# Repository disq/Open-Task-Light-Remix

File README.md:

# Open Task Light Remix

## ⚠️ NOT FINISHED YET

This is a work in progress: parts are still being printed, tested and changed.

A remix of [Open Task Light](https://github.com/stevenbennett/Open-Task-Light) by Steven Bennett: a new control board for the head running ESPHome, a USB-C PD board in the freestanding base with the printed parts to hold it, and fixes for printed parts that don't fit. The rest of the lamp is built as upstream.

| Folder | What's in it |
|---|---|
| [`electronics/`](electronics/) | KiCad 10 projects, Gerbers, BOMs and JLC placement files for two boards: the head's control board, reworked around a Seeed XIAO ESP32-C6, and a USB-PD board that powers the lamp at 20 V from a USB-C charger. |
| [`esphome/`](esphome/) | ESPHome firmware for the control board, for Home Assistant. |
| [`mechanical/`](mechanical/) | Printed parts: the freestanding base reworked for the PD board, wider button sockets for the electronics housing, and a lead counterweight lid that goes in. |

Each folder has its own README with the details.

## Licence

MIT, like upstream. See [LICENSE](LICENSE).

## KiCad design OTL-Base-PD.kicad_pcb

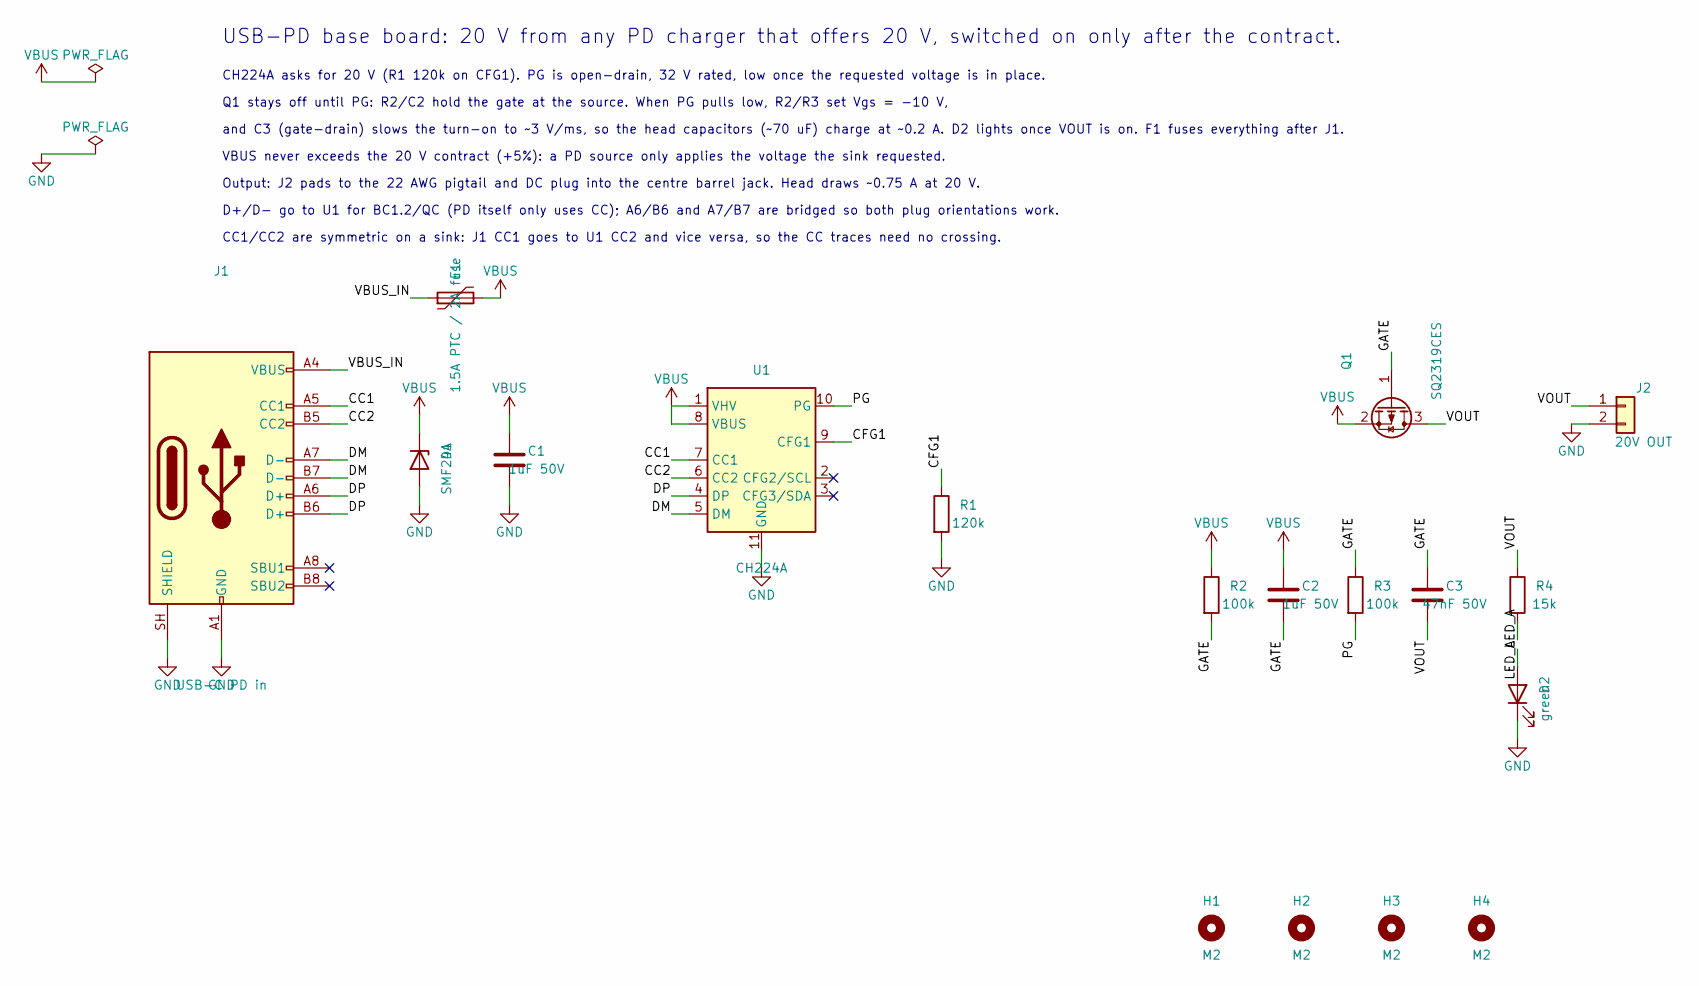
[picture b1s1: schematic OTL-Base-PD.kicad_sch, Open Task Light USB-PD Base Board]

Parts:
C1, C2: 1uF 50V; C_0805_2012Metric; MPN CL21B105KBFNNNE; LCSC Part C28323
C3: 47nF 50V; C_0603_1608Metric; MPN CL10B473KB8NNNC; LCSC Part C1622
D1: SMF24A; SOD-123F_L2.8-W1.8-LS3.7-RD; MPN SMF24A; LCSC Part C169430
D2: green; LED_0603_1608Metric; MPN XL-1608UGC-04; LCSC Part C965804
F1: 1.5A PTC / 2A fuse; Fuse_1812_1206_Dual; MPN SMD1812P150TF/33 (or Littelfuse 0466002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; LCSC Part C46970909
H1, H2, H3, H4: M2; MountingHole_2.2mm_M2
J1: USB-C PD in; USB_C_Receptacle_HRO_TYPE-C-31-M-12; MPN TYPE-C-31-M-12; LCSC Part C165948
J2: 20V OUT; SolderWire-0.5sqmm_1x02_P4.6mm_D0.9mm_OD2.1mm
Q1: SQ2319CES; SOT-23; MPN SQ2319CES-T1_GE3 (or AO3407A); LCSC Part C30884362
R1: 120k; R_0603_1608Metric; MPN 0603WAF1203T5E; LCSC Part C25808
R2, R3: 100k; R_0603_1608Metric; MPN 0603WAF1003T5E; LCSC Part C25803
R4: 15k; R_0603_1608Metric; MPN 0603WAF1502T5E; LCSC Part C22809
U1: CH224A; SSOP-10-1EP_3.9x4.9mm_P1mm_EP2.1x3.3mm_ThermalVias; MPN CH224A; LCSC Part C42459160

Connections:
/CC1: J1.A5 (CC1), U1.7 (CC1)
/CC2: J1.B5 (CC2), U1.6 (CC2)
/CFG1: R1.1, U1.9 (CFG1)
/DM: J1.A7 (D-), J1.B7 (D-), U1.5 (DM)
/DP: J1.A6 (D+), J1.B6 (D+), U1.4 (DP)
/GATE: C2.2, C3.1, Q1.1 (G), R2.2, R3.1
/LED_A: D2.2 (A), R4.2
/PG: R3.2, U1.10 (PG)
/VBUS_IN: F1.1, J1.A4 (VBUS), J1.A9 (VBUS), J1.B4 (VBUS), J1.B9 (VBUS)
/VOUT: C3.2, J2.1, Q1.3 (D), R4.1
GND: C1.2, D1.2 (A), D2.1 (K), J1.A1 (GND), J1.A12 (GND), J1.B1 (GND), J1.B12 (GND), J1.SH (SHIELD), J2.2, R1.2, U1.11 (GND)
VBUS: C1.1, C2.1, D1.1 (K), F1.2, Q1.2 (S), R2.1, U1.1 (VHV), U1.8 (VBUS)

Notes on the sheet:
CC1/CC2 are symmetric on a sink: J1 CC1 goes to U1 CC2 and vice versa, so the CC traces need no crossing.
VBUS never exceeds the 20 V contract (+5%): a PD source only applies the voltage the sink requested.
and C3 (gate-drain) slows the turn-on to ~3 V/ms, so the head capacitors (~70 uF) charge at ~0.2 A. D2 lights once VOUT is on. F1 fuses everything after J1.
D+/D- go to U1 for BC1.2/QC (PD itself only uses CC); A6/B6 and A7/B7 are bridged so both plug orientations work.
CH224A asks for 20 V (R1 120k on CFG1). PG is open-drain, 32 V rated, low once the requested voltage is in place.
USB-PD base board: 20 V from any PD charger that offers 20 V, switched on only after the contract.
Output: J2 pads to the 22 AWG pigtail and DC plug into the centre barrel jack. Head draws ~0.75 A at 20 V.
Q1 stays off until PG: R2/C2 hold the gate at the source. When PG pulls low, R2/R3 set Vgs = -10 V,

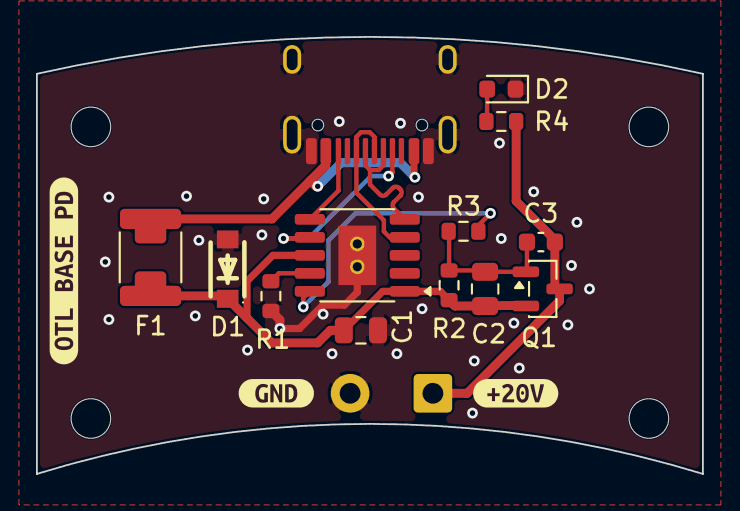
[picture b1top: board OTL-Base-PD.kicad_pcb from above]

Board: 2 copper layers, 37.0 x 24.3 mm, 21 parts (0 on the bottom side), 12 nets.

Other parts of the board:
kibuzzard-6ACABDDA: G***; kibuzzard-6ACABDDA
kibuzzard-6ACABDE6: G***; kibuzzard-6ACABDE6
kibuzzard-6ACABDF7: G***; kibuzzard-6ACABDF7

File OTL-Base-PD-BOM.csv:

"Comment","Designator","Footprint","LCSC Part #","MPN","Qty"
"1uF 50V","C1,C2","Capacitor_SMD:C_0805_2012Metric","C28323","CL21B105KBFNNNE","2"
"47nF 50V","C3","Capacitor_SMD:C_0603_1608Metric","C1622","CL10B473KB8NNNC","1"
"SMF24A","D1","EasyEDA:SOD-123F_L2.8-W1.8-LS3.7-RD","C169430","SMF24A","1"
"green","D2","LED_SMD:LED_0603_1608Metric","C965804","XL-1608UGC-04","1"
"1.5A PTC / 2A fuse","F1","OTL:Fuse_1812_1206_Dual","C46970909","SMD1812P150TF/33 (or Littelfuse 0466002.NRHF 1206 2A fuse)","1"
"USB-C PD in","J1","Connector_USB:USB_C_Receptacle_HRO_TYPE-C-31-M-12","C165948","TYPE-C-31-M-12","1"
"SQ2319CES","Q1","Package_TO_SOT_SMD:SOT-23","C30884362","SQ2319CES-T1_GE3 (or AO3407A)","1"
"120k","R1","Resistor_SMD:R_0603_1608Metric","C25808","0603WAF1203T5E","1"
"100k","R2,R3","Resistor_SMD:R_0603_1608Metric","C25803","0603WAF1003T5E","2"
"15k","R4","Resistor_SMD:R_0603_1608Metric","C22809","0603WAF1502T5E","1"
"CH224A","U1","Package_SO:SSOP-10-1EP_3.9x4.9mm_P1mm_EP2.1x3.3mm_ThermalVias","C42459160","CH224A","1"

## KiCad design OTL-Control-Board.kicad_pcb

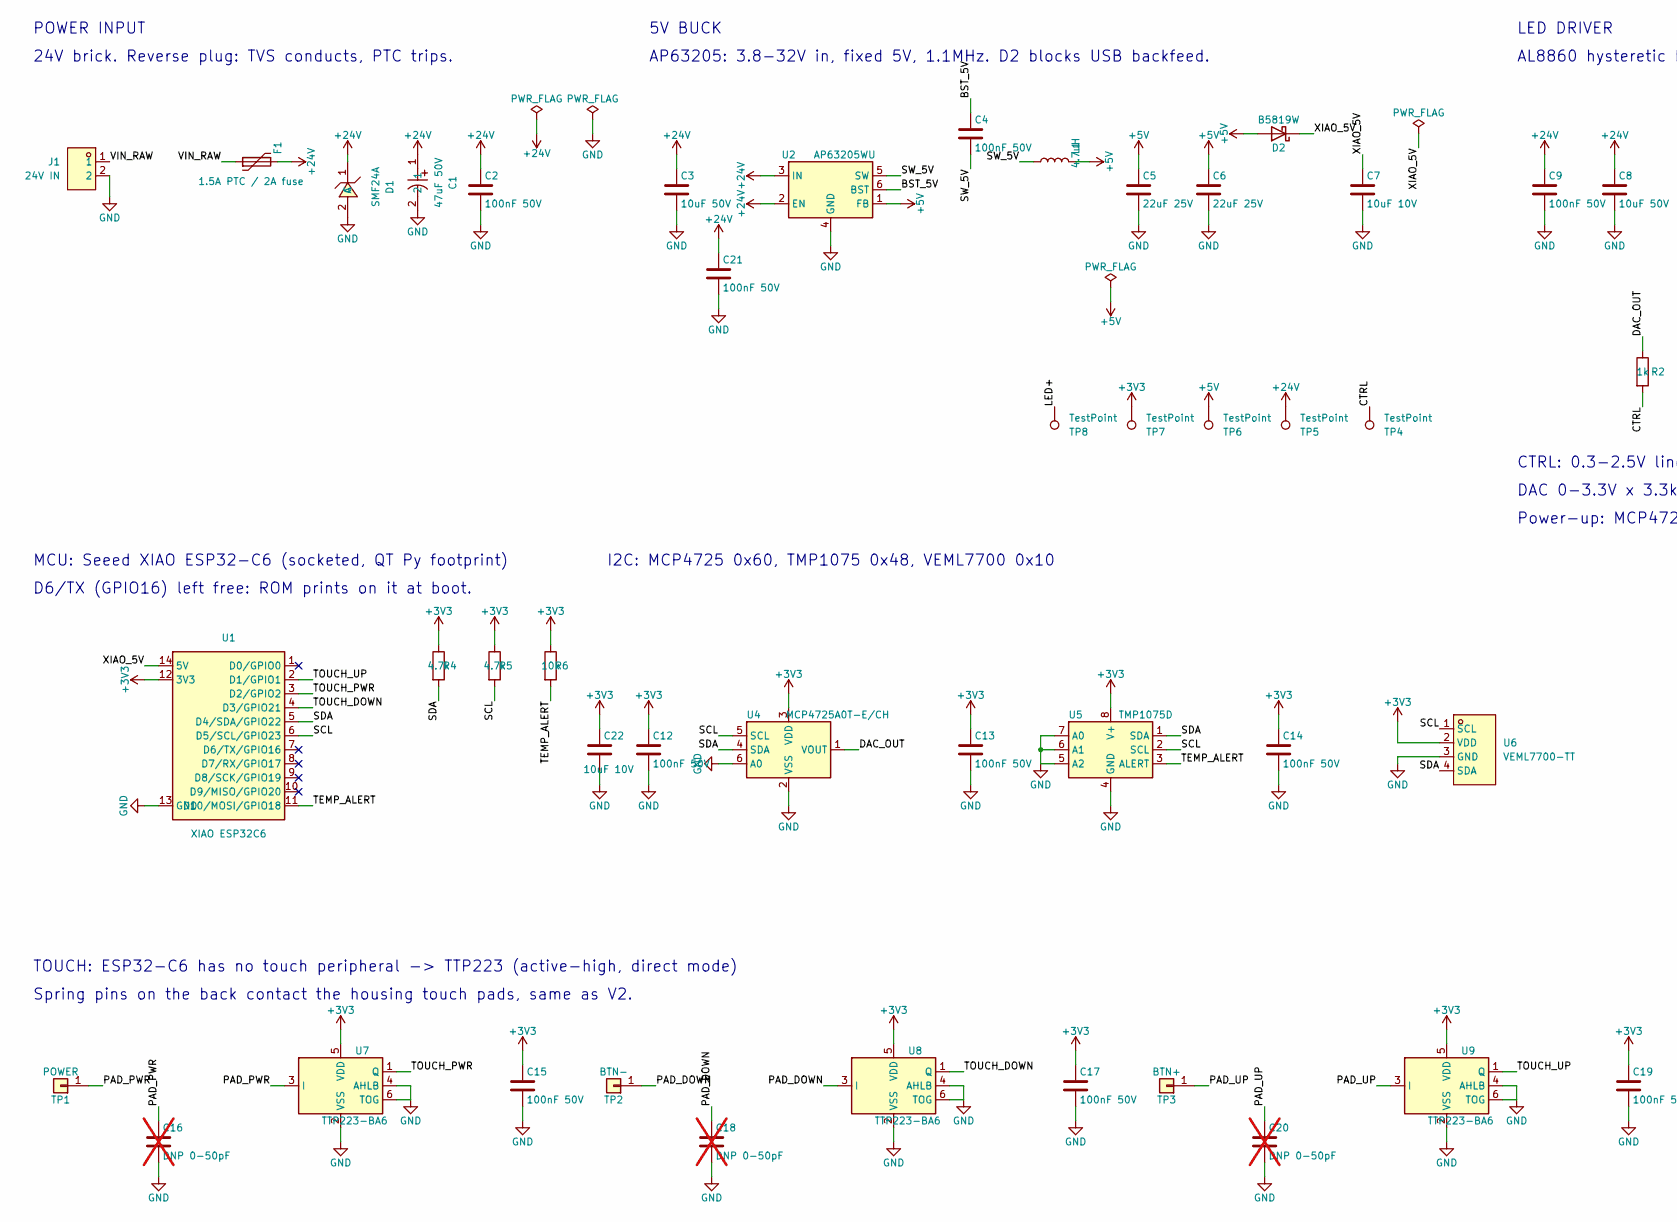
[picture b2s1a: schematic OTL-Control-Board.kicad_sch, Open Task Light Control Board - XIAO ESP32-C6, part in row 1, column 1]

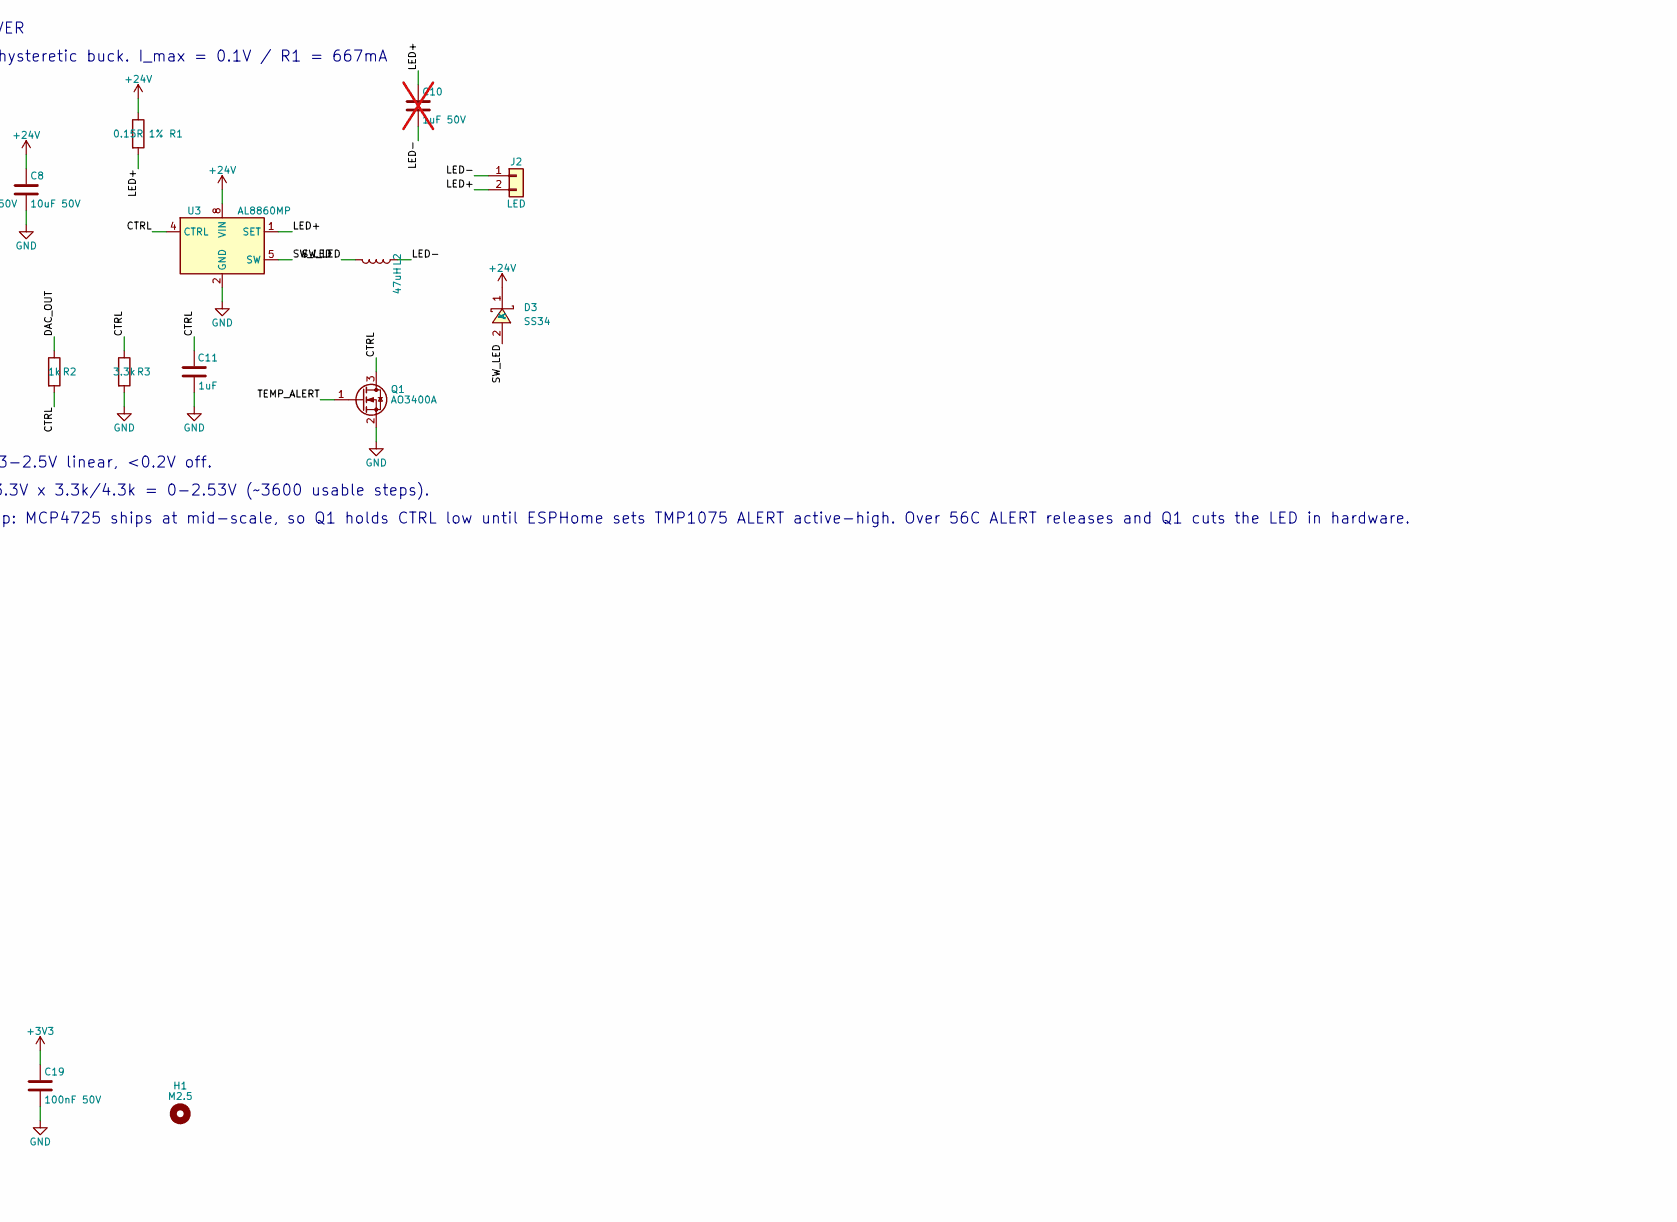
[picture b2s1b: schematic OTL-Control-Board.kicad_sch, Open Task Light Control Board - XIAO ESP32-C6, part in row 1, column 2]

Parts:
C1: 47uF 50V; CAP-SMD_BD6.3-L6.6-W6.6-FD-A; MPN VZT470M1HTR-0606; LCSC Part C688950
C2, C4, C9, C12, C13, C14, C15, C17, C19: 100nF 50V; C_0603_1608Metric; MPN CC0603KRX7R9BB104; LCSC Part C14663
C3, C8: 10uF 50V; C_1206_3216Metric; MPN 1206 X5R/X7R 10uF 50V; LCSC Part C13585
C5, C6: 22uF 25V; C_1206_3216Metric; MPN 1206 X5R 22uF 25V (CL31A226KAHNNNE); LCSC Part C12891
C7, C22: 10uF 10V; C_0805_2012Metric; MPN 0805 X5R 10uF 10V; LCSC Part C15850
C10: 1uF 50V; C_1206_3216Metric; MPN 1206 X7R 1uF 50V (optional ripple cap); LCSC Part C1848; not fitted
C11: 1uF; C_0603_1608Metric; MPN 0603 X5R 1uF; LCSC Part C15849
C16, C18, C20: DNP 0-50pF; C_0603_1608Metric; MPN sensitivity trim, C0G; not fitted
C21: 100nF 50V; C_0805_2012Metric; MPN 0805 X7R 100nF 50V (CC0805KRX7R9BB104); LCSC Part C49678
D1: SMF24A; SOD-123F_L2.8-W1.8-LS3.7-RD; MPN SMF24A; LCSC Part C169430
D2: B5819W; D_SOD-123; MPN B5819W; LCSC Part C8598
D3: SS34; SMA_L4.3-W2.6-LS5.2-RD; MPN SS34; LCSC Part C8678
F1: 1.5A PTC / 2A fuse; Fuse_1812_1206_Dual; MPN SMD1812P150TF/33 (1812 PTC, JLC reflow)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; LCSC Part C46970909
H1: M2.5; MountingHole_2.5mm_Plated
J1: 24V IN; CONN-TH_2P-P1.25-220098-0271; MPN 2200980271; LCSC Part C19803189
J2: LED; Molex_MicroLock_2200970271_V; MPN Molex 2200970271; LCSC Part C19803164
L1: 4.7uH; L_Changjiang_FNR4030S; MPN FNR4030S4R7MT (4x4, Isat>=1.5A); LCSC Part C167874
L2: 47uH; L_SRN1060_FNR8040_Dual; MPN FNR8040S470MT (8x8) or SRN1060-470M (10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; LCSC Part C168137
Q1: AO3400A; SOT-23; MPN AO3400A; LCSC Part C20917
R1: 0.15R 1%; R_1206_3216Metric; MPN 1206 0.15R 1% 0.25W; LCSC Part C5127776
R2: 1k; R_0603_1608Metric; MPN 0603 1k 1%; LCSC Part C21190
R3: 3.3k; R_0603_1608Metric; MPN 0603 3.3k 1%; LCSC Part C22978
R4, R5: 4.7k; R_0603_1608Metric; MPN 0603 4.7k; LCSC Part C23162
R6: 10k; R_0603_1608Metric; MPN 0603 10k; LCSC Part C25804
TP1: POWER; MillMax_807_SpringPin; MPN Mill-Max 807-22-001-10-001101
TP2: BTN-; MillMax_807_SpringPin; MPN Mill-Max 807-22-001-10-001101
TP3: BTN+; MillMax_807_SpringPin; MPN Mill-Max 807-22-001-10-001101
TP4, TP5, TP6, TP7, TP8: TestPoint; TestPoint_Pad_1.5x1.5mm
U1: XIAO ESP32C6; XIAO_Socket_2x7; MPN Seeed XIAO ESP32-C6 + 2x Samtec CES-107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
U2: AP63205WU; TSOT-23-6; MPN AP63205WU-7; LCSC Part C2071056
U3: AL8860MP; MSOP-8-1EP_3x3mm_P0.65mm_EP1.5x1.8mm; MPN AL8860MP-13; LCSC Part C500782
U4: MCP4725A0T-E/CH; SOT-23-6; MPN MCP4725A0T-E/CH; LCSC Part C144198
U5: TMP1075D; SOIC-8_3.9x4.9mm_P1.27mm; MPN TMP1075DR; LCSC Part C2878381
U6: VEML7700-TT; SENSOR-SMD_EML7700-TT; MPN VEML7700-TT; LCSC Part C1850416
U7, U8, U9: TTP223-BA6; SOT-23-6; MPN TTP223-BA6 or TTP223-BA6-TD; LCSC Part C42422127

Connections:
+3V3: C12.1, C13.1, C14.1, C15.1, C17.1, C19.1, C22.1, R4.1, R5.1, R6.1, TP7.1 (1_1), U1.12 (3V3), U4.3 (VDD), U5.8 (V+), U6.2 (VDD), U7.5 (VDD), U8.5 (VDD), U9.5 (VDD)
+5V: C5.1, C6.1, D2.2 (A), L1.2, TP6.1 (1_1), U2.1 (FB)
+24V: C1.1, C2.1, C3.1, C8.1, C9.1, C21.1, D1.1 (C), D3.1 (K), F1.2, R1.1, TP5.1 (1_1), U2.2 (EN), U2.3 (IN), U3.8 (VIN)
/BST_5V: C4.1, U2.6 (BST)
/CTRL: C11.1, Q1.3 (D), R2.2, R3.1, TP4.1 (1_1), U3.4 (CTRL)
/DAC_OUT: R2.1, U4.1 (VOUT)
/LED+: C10.1, J2.2, R1.2, TP8.1 (1_1), U3.1 (SET)
/LED-: C10.2, J2.1, L2.1
/PAD_DOWN: C18.1, TP2.1 (Pin_1_1), U8.3 (I)
/PAD_PWR: C16.1, TP1.1 (Pin_1_1), U7.3 (I)
/PAD_UP: C20.1, TP3.1 (Pin_1_1), U9.3 (I)
/SCL: R5.2, U1.6 (D5/SCL/GPIO23), U4.5 (SCL), U5.2 (SCL), U6.1 (SCL)
/SDA: R4.2, U1.5 (D4/SDA/GPIO22), U4.4 (SDA), U5.1 (SDA), U6.4 (SDA)
/SW_5V: C4.2, L1.1, U2.5 (SW)
/SW_LED: D3.2 (A), L2.2, U3.5 (SW), U3.6 (SW)
/TEMP_ALERT: Q1.1 (G), R6.2, U1.11 (D10/MOSI/GPIO18), U5.3 (ALERT)
/TOUCH_DOWN: U1.4 (D3/GPIO21), U8.1 (Q)
/TOUCH_PWR: U1.3 (D2/GPIO2), U7.1 (Q)
/TOUCH_UP: U1.2 (D1/GPIO1), U9.1 (Q)
/VIN_RAW: F1.1, J1.1
/XIAO_5V: C7.1, D2.1 (K), U1.14 (5V)
GND: C1.2, C2.2, C3.2, C5.2, C6.2, C7.2, C8.2, C9.2, C11.2, C12.2, C13.2, C14.2, C15.2, C16.2, C17.2, C18.2, C19.2, C20.2, C21.2, C22.2, D1.2 (A), J1.2, Q1.2 (S), R3.2, U1.13 (GND), U2.4 (GND), U3.2 (GND), U3.3 (GND), U3.9 (GND), U4.2 (VSS), U4.6 (A0), U5.4 (GND), U5.5 (A2), U5.6 (A1), U5.7 (A0), U6.3 (GND), U7.2 (VSS), U7.4 (AHLB), U7.6 (TOG), U8.2 (VSS), U8.4 (AHLB), U8.6 (TOG), U9.2 (VSS), U9.4 (AHLB), U9.6 (TOG)

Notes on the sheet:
AP63205: 3.8-32V in, fixed 5V, 1.1MHz. D2 blocks USB backfeed.
D6/TX (GPIO16) left free: ROM prints on it at boot.
DAC 0-3.3V x 3.3k/4.3k = 0-2.53V (~3600 usable steps).
AL8860 hysteretic buck. I_max = 0.1V / R1 = 667mA
24V brick. Reverse plug: TVS conducts, PTC trips.
TOUCH: ESP32-C6 has no touch peripheral -> TTP223 (active-high, direct mode)
Power-up: MCP4725 ships at mid-scale, so Q1 holds CTRL low until ESPHome sets TMP1075 ALERT active-high. Over 56C ALERT releases and Q1 cuts the LED in hardware.
I2C: MCP4725 0x60, TMP1075 0x48, VEML7700 0x10
MCU: Seeed XIAO ESP32-C6 (socketed, QT Py footprint)
LED DRIVER
5V BUCK
Spring pins on the back contact the housing touch pads, same as V2.
POWER INPUT
CTRL: 0.3-2.5V linear, <0.2V off.

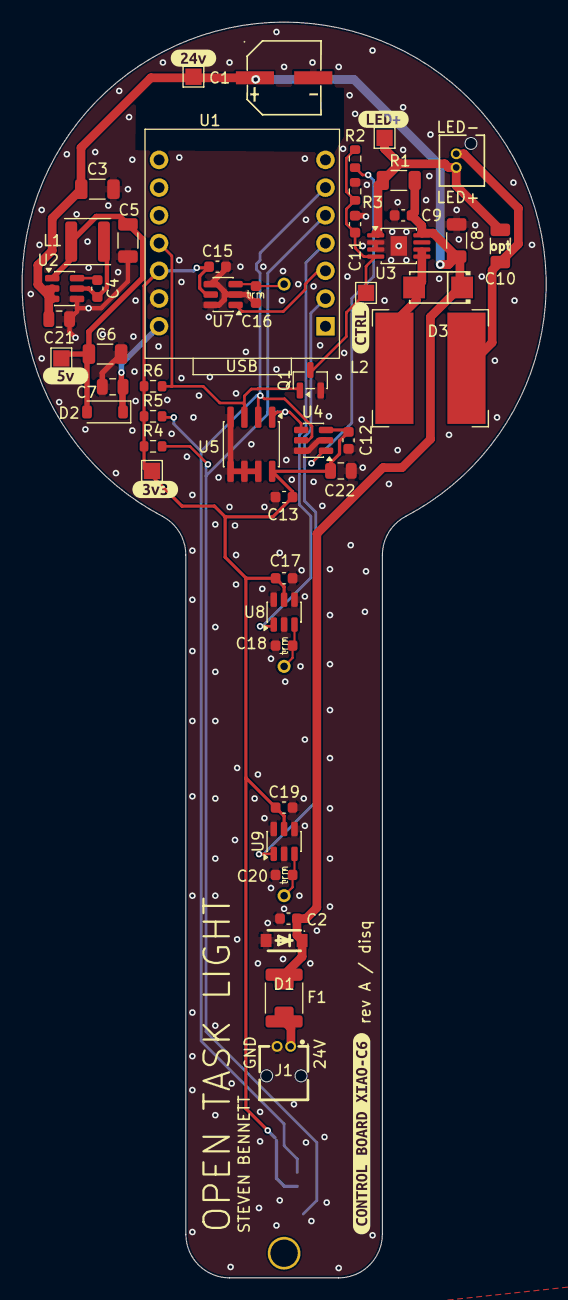
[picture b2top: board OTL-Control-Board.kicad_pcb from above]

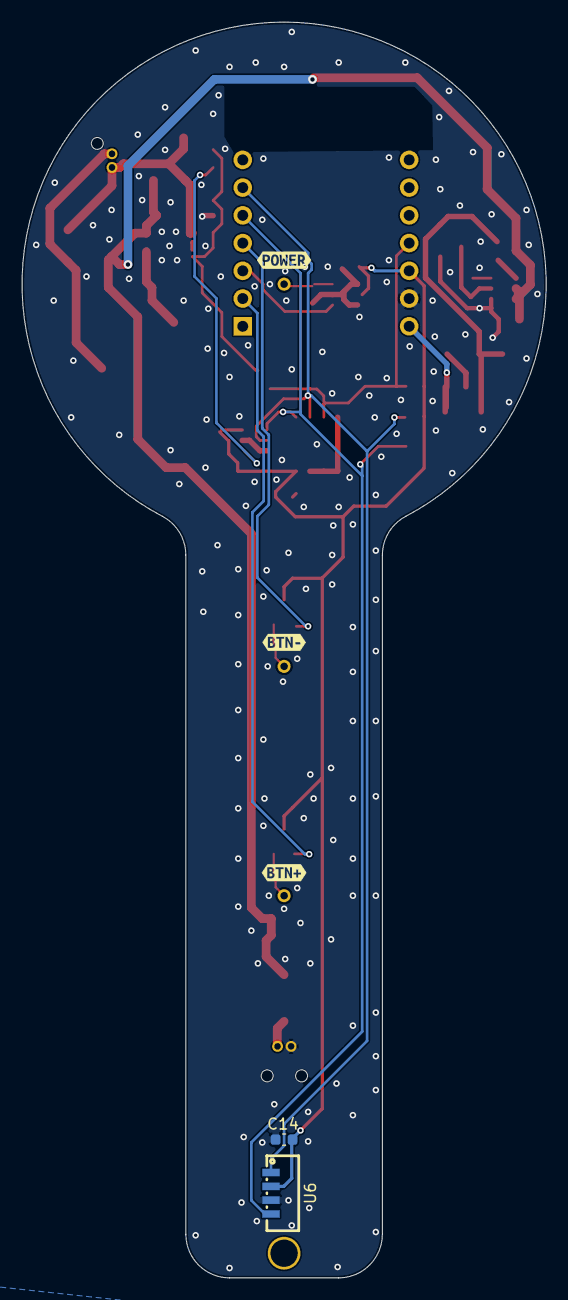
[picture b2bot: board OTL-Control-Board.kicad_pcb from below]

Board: 2 copper layers, 48.0 x 115.0 mm, 64 parts (8 on the bottom side), 22 nets.

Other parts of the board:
kibuzzard-6AC8A8F0: G***; kibuzzard-6AC8A8F0
kibuzzard-6AC8A80C: G***; kibuzzard-6AC8A80C
kibuzzard-6AC8A84C: G***; kibuzzard-6AC8A84C
kibuzzard-6AC8A90C: G***; kibuzzard-6AC8A90C
kibuzzard-6AC8A96E: G***; kibuzzard-6AC8A96E
kibuzzard-6AC8A820: G***; kibuzzard-6AC8A820
kibuzzard-6AC8A893: G***; kibuzzard-6AC8A893
kibuzzard-6AC8A927: G***; kibuzzard-6AC8A927
kibuzzard-6AC8A951: G***; kibuzzard-6AC8A951

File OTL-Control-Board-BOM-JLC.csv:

"Comment","Designator","Footprint","LCSC Part #"
"47uF 50V","C1","EasyEDA:CAP-SMD_BD6.3-L6.6-W6.6-FD-A","C688950"
"100nF 50V","C2,C9","Capacitor_SMD:C_0603_1608Metric","C14663"
"10uF 50V","C3,C8","Capacitor_SMD:C_1206_3216Metric","C13585"
"100nF","C4,C12,C13,C14,C15,C17,C19","Capacitor_SMD:C_0603_1608Metric","C14663"
"22uF 25V","C5,C6","Capacitor_SMD:C_1206_3216Metric","C12891"
"10uF 10V","C7,C22","Capacitor_SMD:C_0805_2012Metric","C15850"
"1uF","C11","Capacitor_SMD:C_0603_1608Metric","C15849"
"100nF 50V","C21","Capacitor_SMD:C_0805_2012Metric","C49678"
"SMF24A","D1","EasyEDA:SOD-123F_L2.8-W1.8-LS3.7-RD","C169430"
"B5819W","D2","Diode_SMD:D_SOD-123","C8598"
"SS34","D3","EasyEDA:SMA_L4.3-W2.6-LS5.2-RD","C8678"
"1.5A PTC / 2A fuse","F1","OTL:Fuse_1812_1206_Dual","C46970909"
"M2.5","H1","OTL:MountingHole_2.5mm_Plated",""
"24V IN","J1","EasyEDA:CONN-TH_2P-P1.25-220098-0271","C19803189"
"LED","J2","OTL:Molex_MicroLock_2200970271_V","C19803164"
"4.7uH","L1","Inductor_SMD:L_Changjiang_FNR4030S","C167874"
"47uH","L2","OTL:L_SRN1060_FNR8040_Dual","C168137"
"AO3400A","Q1","Package_TO_SOT_SMD:SOT-23","C20917"
"0.15R 1%","R1","Resistor_SMD:R_1206_3216Metric","C5127776"
"1k","R2","Resistor_SMD:R_0603_1608Metric","C21190"
"3.3k","R3","Resistor_SMD:R_0603_1608Metric","C22978"
"4.7k","R4,R5","Resistor_SMD:R_0603_1608Metric","C23162"
"10k","R6","Resistor_SMD:R_0603_1608Metric","C25804"
"POWER","TP1","OTL:MillMax_807_SpringPin",""
"BTN-","TP2","OTL:MillMax_807_SpringPin",""
"BTN+","TP3","OTL:MillMax_807_SpringPin",""
"XIAO ESP32C6","U1","OTL:XIAO_Socket_2x7",""
"AP63205WU","U2","Package_TO_SOT_SMD:TSOT-23-6","C2071056"
"AL8860MP","U3","Package_SO:MSOP-8-1EP_3x3mm_P0.65mm_EP1.5x1.8mm","C500782"
"MCP4725A0T-E/CH","U4","Package_TO_SOT_SMD:SOT-23-6","C144198"
"TMP1075D","U5","Package_SO:SOIC-8_3.9x4.9mm_P1.27mm","C2878381"
"VEML7700-TT","U6","EasyEDA:SENSOR-SMD_EML7700-TT","C1850416"
"TTP223-BA6","U7,U8,U9","Package_TO_SOT_SMD:SOT-23-6","C42422127"

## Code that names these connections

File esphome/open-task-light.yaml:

substitutions:
  name: open-task-light
  friendly_name: Open Task Light

esphome:
  name: ${name}
  friendly_name: ${friendly_name}
  on_boot:
    # Runs after all components are set up, so it overrides the tmp1075 driver's config write.
    # The driver's bitfield is reversed against the TMP1075 CFGR MSB (OS R1 R0 F1 F0 POL TM SD), so its
    # polarity option lands on R0 and ALERT stays active-low. 0x64 = 220ms rate, 1 fault, POL=1, comparator.
    priority: -100
    then:
      - lambda: |-
          if (!id(board_temp).write_byte(0x01, 0x64)) {
            ESP_LOGE("tmp1075", "Failed to set ALERT active-high");
          }

esp32:
  board: seeed_xiao_esp32c6
  variant: esp32c6
  framework:
    type: esp-idf

logger:

api:
  encryption:
    key: !secret api_encryption_key

ota:
  - platform: esphome
    encryption:

wifi:
  ssid: !secret wifi_ssid
  password: !secret wifi_password
  ap:
    password: !secret ap_password

captive_portal:

# Set Wi-Fi over USB after flashing (web.esphome.io > Connect > Configure Wi-Fi).
improv_serial:

i2c:
  sda: GPIO22  # D4
  scl: GPIO23  # D5
  frequency: 400kHz

switch:
  # XIAO ESP32-C6 RF switch: ESP-IDF doesn't set these up the way the Arduino core does.
  - platform: gpio
    id: rf_switch_enable
    pin: GPIO3  # low = RF switch powered
    restore_mode: ALWAYS_OFF
    internal: true
  - platform: gpio
    id: rf_antenna_select
    pin: GPIO14  # low = onboard ceramic antenna, high = U.FL
    restore_mode: ALWAYS_OFF
    internal: true

output:
  - platform: mcp4725
    id: led_dac
    address: 0x60
    # AL8860 CTRL is linear from 0.3V (0%) to 2.5V (100%). The 3.3k/4.3k divider maps DAC full scale to 2.53V.
    # 0.17 x 2.53V = 0.43V, about 6% of full current (~40mA) at 1% brightness: inside the AL8860's recommended
    # 5-100% analog dimming range, with margin over the MCP4725 offset, 1% resistors and the 3V3 tolerance.
    min_power: 0.17
    zero_means_zero: true

light:
  - platform: monochromatic
    id: lamp
    name: Lamp
    output: led_dac
    gamma_correct: 2.2
    default_transition_length: 400ms
    restore_mode: RESTORE_DEFAULT_OFF
    # Catches every turn-on path (touch, Home Assistant, restore) while the board is over temperature.
    on_turn_on:
      - if:
          condition:
            binary_sensor.is_on: over_temperature
          then:
            - light.turn_off: lamp

sensor:
  - platform: tmp1075
    id: board_temp
    name: Board temperature
    update_interval: 10s
    # Same limits as the original firmware (HIGH_TEMP 50, MAX_TEMP 56).
    # The TMP1075 powers up active-low, so ALERT floats high (via R6) and Q1 holds CTRL at 0V: the LED stays off
    # until on_boot switches ALERT to active-high. From then on ALERT only goes high (and Q1 kills the LED in
    # hardware) above 56C, even if the ESP has crashed. Polarity/function are set in on_boot, not here.
    alert:
      limit_high: 56
      limit_low: 50

  - platform: wifi_signal
    name: Wi-Fi signal
    update_interval: 60s

  - platform: uptime
    name: Uptime

  - platform: veml7700
    address: 0x10
    update_interval: 10s
    ambient_light:
      name: Ambient light

binary_sensor:
  - platform: gpio
    id: touch_power
    name: Touch power
    pin: GPIO2  # D2, U7
    filters:
      - delayed_on: 20ms
    on_press:
      then:
        - if:
            condition:
              light.is_on: lamp
            then:
              - light.turn_off: lamp
            else:
              - light.turn_on: lamp

  - platform: gpio
    id: touch_up
    name: Touch up
    pin: GPIO1  # D1, U9
    filters:
      - delayed_on: 20ms
    on_press:
      then:
        - while:
            condition:
              and:
                - binary_sensor.is_on: touch_up
                - light.is_on: lamp
            then:
              - light.dim_relative:
                  id: lamp
                  relative_brightness: 5%
                  transition_length: 100ms
                  brightness_limits:
                    min_brightness: 1%
              - delay: 120ms

  - platform: gpio
    id: touch_down
    name: Touch down
    pin: GPIO21  # D3, U8
    filters:
      - delayed_on: 20ms
    on_press:
      then:
        - while:
            condition:
              and:
                - binary_sensor.is_on: touch_down
                - light.is_on: lamp
            then:
              - light.dim_relative:
                  id: lamp
                  relative_brightness: -5%
                  transition_length: 100ms
                  brightness_limits:
                    min_brightness: 1%
              - delay: 120ms

  - platform: gpio
    id: over_temperature
    name: Over temperature
    device_class: heat
    pin: GPIO18  # D10, TMP1075 ALERT (active-high once configured, R6 pull-up)
    filters:
      # ALERT reads high for a moment at power-up, before the TMP1075 is configured.
      - delayed_on: 2s
    on_press:
      then:
        - light.turn_off: lamp

button:
  - platform: restart
    name: Restart
